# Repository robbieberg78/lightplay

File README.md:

# lightplay
javascript scratch extensions that create blocks to send and receive serial bytes

To see and example, type:

    python -m python_plugin.plugin

If the plugin needs help finding a connected serial device, it will tell you.

Then, with the plugin running, load one of the .sbx files in the examples directory using <a href=http://scratchx.org/> the scratchx website</a>

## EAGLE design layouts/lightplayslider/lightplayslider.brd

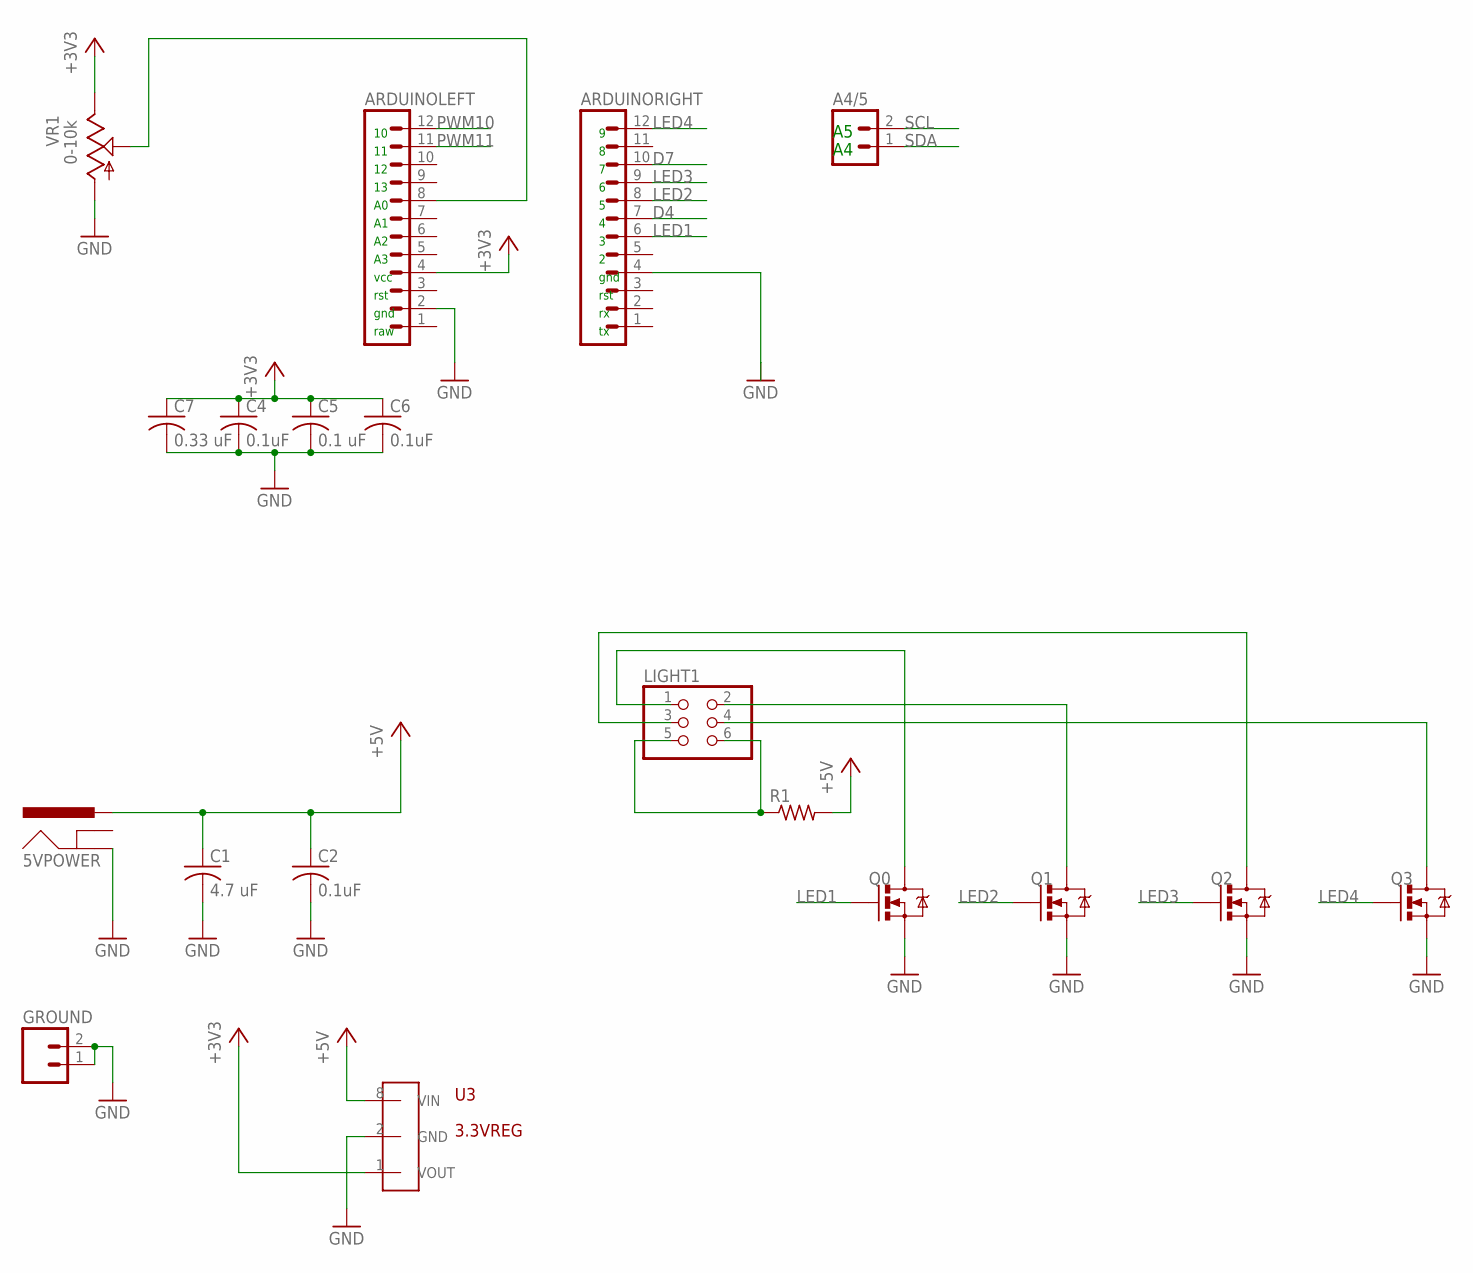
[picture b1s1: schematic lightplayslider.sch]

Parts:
5VPOWER: POWER_JACKPTH; POWER_JACK_PTH
A4/5: M02PTH; 1X02
ARDUINOLEFT: M12PTH; 1X12
ARDUINORIGHT: M12PTH; 1X12
C1: 4.7 uF; C1206
C2, C4, C6: 0.1uF; C0805
C5: 0.1 uF; C0805
C7: 0.33 uF; C1206
GROUND: M02PTH; 1X02
LIGHT1: PINHD-2X3; 2X03
Q0, Q1, Q2, Q3: MOSFET-NCHANNELAO3404A; SOT23-3
R1: R-US_0617/17; 0617/17
U3: 3.3VREG; SO08
VR1: 0-10k; SLIDER-MEDIUM

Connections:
+3V3: ARDUINOLEFT.4, C4.1, C5.1, C6.1, C7.1, U3.1 (VOUT), VR1.TOP (E)
+5V: 5VPOWER.PWR, C1.1, C2.1, R1.2, U3.8 (VIN)
D4: ARDUINORIGHT.7
D7: ARDUINORIGHT.10
GND: 5VPOWER.GND, ARDUINOLEFT.2, ARDUINORIGHT.4, C1.2, C2.2, C4.2, C5.2, C6.2, C7.2, GROUND.1, GROUND.2, Q0.2 (S), Q1.2 (S), Q2.2 (S), Q3.2 (S), U3.2 (GND), VR1.BOTTOM (A)
LED1: ARDUINORIGHT.6, Q0.1 (G)
LED2: ARDUINORIGHT.8, Q1.1 (G)
LED3: ARDUINORIGHT.9, Q2.1 (G)
LED4: ARDUINORIGHT.12, Q3.1 (G)
unnamed: ARDUINOLEFT.8, VR1.WIPER (S)
unnamed: LIGHT1.5, LIGHT1.6, R1.1
unnamed: LIGHT1.1, Q0.3 (D)
unnamed: LIGHT1.2, Q1.3 (D)
unnamed: LIGHT1.3, Q2.3 (D)
unnamed: LIGHT1.4, Q3.3 (D)
PWM10: ARDUINOLEFT.12
PWM11: ARDUINOLEFT.11
SCL: A4/5.2
SDA: A4/5.1

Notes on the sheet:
gnd
rst
raw
vcc

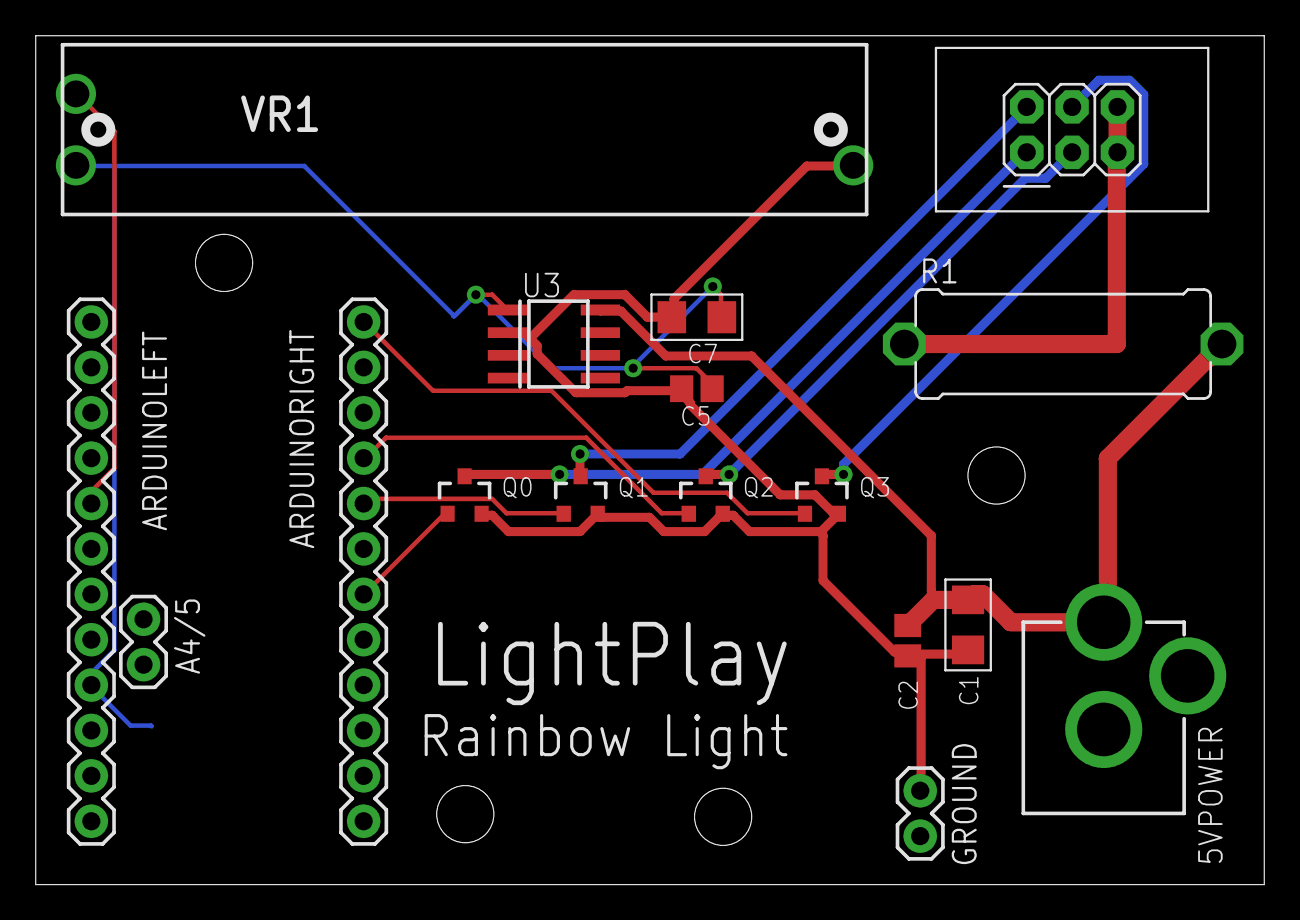
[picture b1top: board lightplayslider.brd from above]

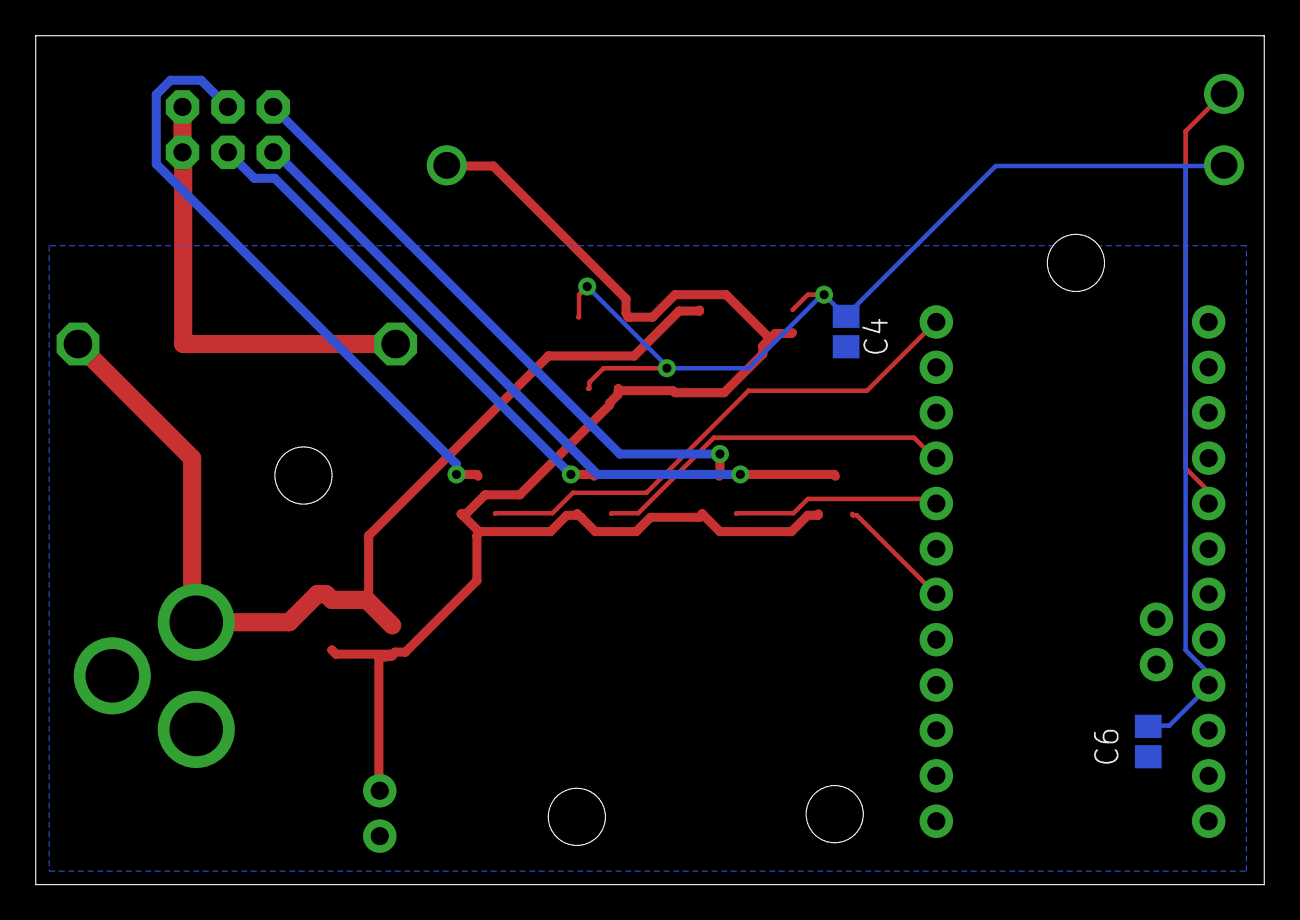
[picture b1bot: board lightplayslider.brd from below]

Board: 2 copper layers, 68.8 x 47.5 mm, 19 parts (2 on the bottom side), 13 nets.

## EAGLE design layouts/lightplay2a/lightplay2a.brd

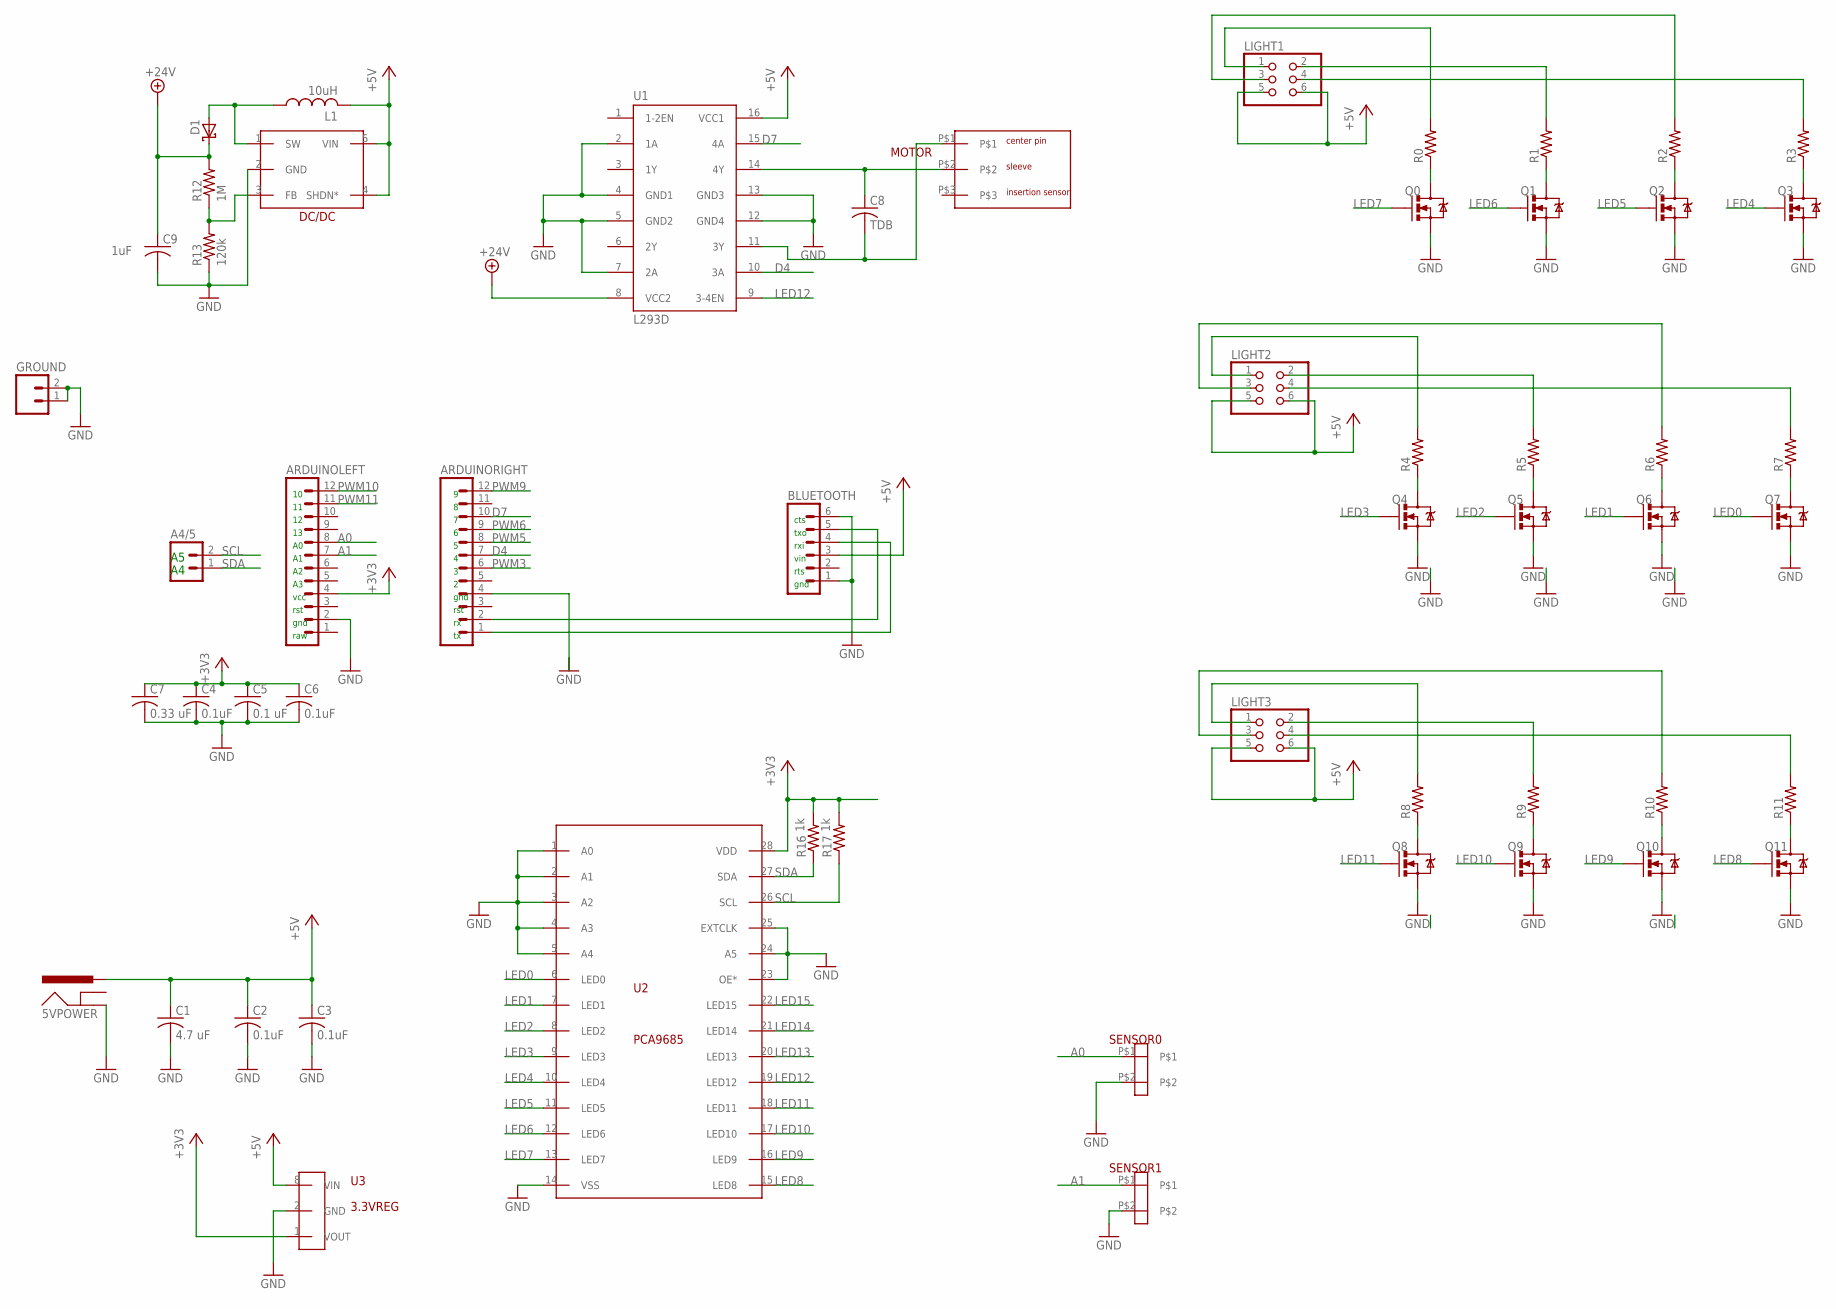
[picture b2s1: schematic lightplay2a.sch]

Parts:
5VPOWER: POWER_JACKPTH; POWER_JACK_PTH
A4/5: M02PTH; 1X02
ARDUINOLEFT: M12PTH; 1X12
ARDUINORIGHT: M12PTH; 1X12
BLUETOOTH: M06SILK_FEMALE_PTH; 1X06
C1: 4.7 uF; C1206
C2, C3, C4, C6: 0.1uF; C0805
C5: 0.1 uF; C0805
C7: 0.33 uF; C1206
C8: TDB; C0805
C9: 1uF; C1206
D1: B120_SHOTTKY_DIODE; DO214AC
DC/DC: LT1615; SOT23-5
GROUND: M02PTH; 1X02
L1: 10uH; INDUCTOR_WURTH
LIGHT1, LIGHT2, LIGHT3: PINHD-2X3; 2X03
MOTOR: PJ-075DH-SMT-TR
Q0, Q1, Q2, Q3, Q4, Q5, Q6, Q7, Q8, Q9, Q10, Q11: MOSFET-NCHANNELAO3404A; SOT23-3
R0, R1, R2, R3, R4, R5, R6, R7, R8, R9, R10, R11: R-US_0617/17; 0617/17
R12: 1M; R0805
R13: 120k; R0805
R16, R17: 1k; R0805
SENSOR0, SENSOR1: 3.5MM_2PIN_SCREWTERMINAL_SPARKFUN; 1X02_3.5_SCREWTERM
U1: L293D; DIL16
U2: PCA9685; TSSOP28
U3: 3.3VREG; SO08

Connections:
+3V3: ARDUINOLEFT.4, C4.1, C5.1, C6.1, C7.1, R16.2, R17.2, U2.28 (VDD), U3.1 (VOUT)
+5V: 5VPOWER.PWR, BLUETOOTH.3, C1.1, C2.1, C3.1, DC/DC.4 (SHDN*), DC/DC.5 (VIN), L1.P$2 (2), LIGHT1.5, LIGHT1.6, LIGHT2.5, LIGHT2.6, LIGHT3.5, LIGHT3.6, U1.16 (VCC1), U3.8 (VIN)
+24V: C9.1, D1.C, R12.2, U1.8 (VCC2)
A0: ARDUINOLEFT.8, SENSOR0.P$1
A1: ARDUINOLEFT.7, SENSOR1.P$1
D4: ARDUINORIGHT.7, U1.10 (3A)
D7: ARDUINORIGHT.10, U1.15 (4A)
GND: 5VPOWER.GND, ARDUINOLEFT.2, ARDUINORIGHT.4, BLUETOOTH.1, BLUETOOTH.6, C1.2, C2.2, C3.2, C4.2, C5.2, C6.2, C7.2, C9.2, DC/DC.2 (GND), GROUND.1, GROUND.2, Q0.2 (S), Q1.2 (S), Q2.2 (S), Q3.2 (S), Q4.2 (S), Q5.2 (S), Q6.2 (S), Q7.2 (S), Q8.2 (S), Q9.2 (S), Q10.2 (S), Q11.2 (S), R13.1, SENSOR0.P$2, SENSOR1.P$2, U1.2 (1A), U1.4 (GND1), U1.5 (GND2), U1.7 (2A), U1.12 (GND4), U1.13 (GND3), U2.1 (A0), U2.2 (A1), U2.3 (A2), U2.4 (A3), U2.5 (A4), U2.14 (VSS), U2.23 (OE*), U2.24 (A5), U2.25 (EXTCLK), U3.2 (GND)
LED0: Q7.1 (G), U2.6 (LED0)
LED1: Q6.1 (G), U2.7 (LED1)
LED2: Q5.1 (G), U2.8 (LED2)
LED3: Q4.1 (G), U2.9 (LED3)
LED4: Q3.1 (G), U2.10 (LED4)
LED5: Q2.1 (G), U2.11 (LED5)
LED6: Q1.1 (G), U2.12 (LED6)
LED7: Q0.1 (G), U2.13 (LED7)
LED8: Q11.1 (G), U2.15 (LED8)
LED9: Q10.1 (G), U2.16 (LED9)
LED10: Q9.1 (G), U2.17 (LED10)
LED11: Q8.1 (G), U2.18 (LED11)
LED12: U1.9 (3-4EN), U2.19 (LED12)
LED13: U2.20 (LED13)
LED14: U2.21 (LED14)
LED15: U2.22 (LED15)
unnamed: Q0.3 (D), R0.1
unnamed: Q1.3 (D), R1.1
unnamed: Q2.3 (D), R2.1
unnamed: C8.1, MOTOR.P$2, U1.14 (4Y)
unnamed: C8.2, MOTOR.P$1, U1.11 (3Y)
unnamed: D1.A, DC/DC.1 (SW), L1.P$1 (1)
unnamed: LIGHT1.1, R0.2
unnamed: Q3.3 (D), R3.1
unnamed: LIGHT1.2, R1.2
unnamed: ARDUINORIGHT.2, BLUETOOTH.5
unnamed: ARDUINORIGHT.1, BLUETOOTH.4
unnamed: Q4.3 (D), R4.1
unnamed: LIGHT1.3, R2.2
unnamed: LIGHT1.4, R3.2
unnamed: Q5.3 (D), R5.1
unnamed: Q6.3 (D), R6.1
unnamed: Q7.3 (D), R7.1
unnamed: LIGHT2.1, R4.2
unnamed: LIGHT2.2, R5.2
unnamed: LIGHT2.3, R6.2
unnamed: LIGHT2.4, R7.2
unnamed: Q8.3 (D), R8.1
unnamed: Q9.3 (D), R9.1
unnamed: Q10.3 (D), R10.1
unnamed: Q11.3 (D), R11.1
unnamed: LIGHT3.1, R8.2
unnamed: LIGHT3.2, R9.2
unnamed: LIGHT3.3, R10.2
unnamed: LIGHT3.4, R11.2
unnamed: DC/DC.3 (FB), R12.1, R13.2
PWM3: ARDUINORIGHT.6
PWM5: ARDUINORIGHT.8
PWM6: ARDUINORIGHT.9
PWM9: ARDUINORIGHT.12
PWM10: ARDUINOLEFT.12
PWM11: ARDUINOLEFT.11
SCL: A4/5.2, R17.1, U2.26 (SCL)
SDA: A4/5.1, R16.1, U2.27 (SDA)

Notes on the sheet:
gnd
rst
raw
vcc
rts
vin
rxi
txo
cts

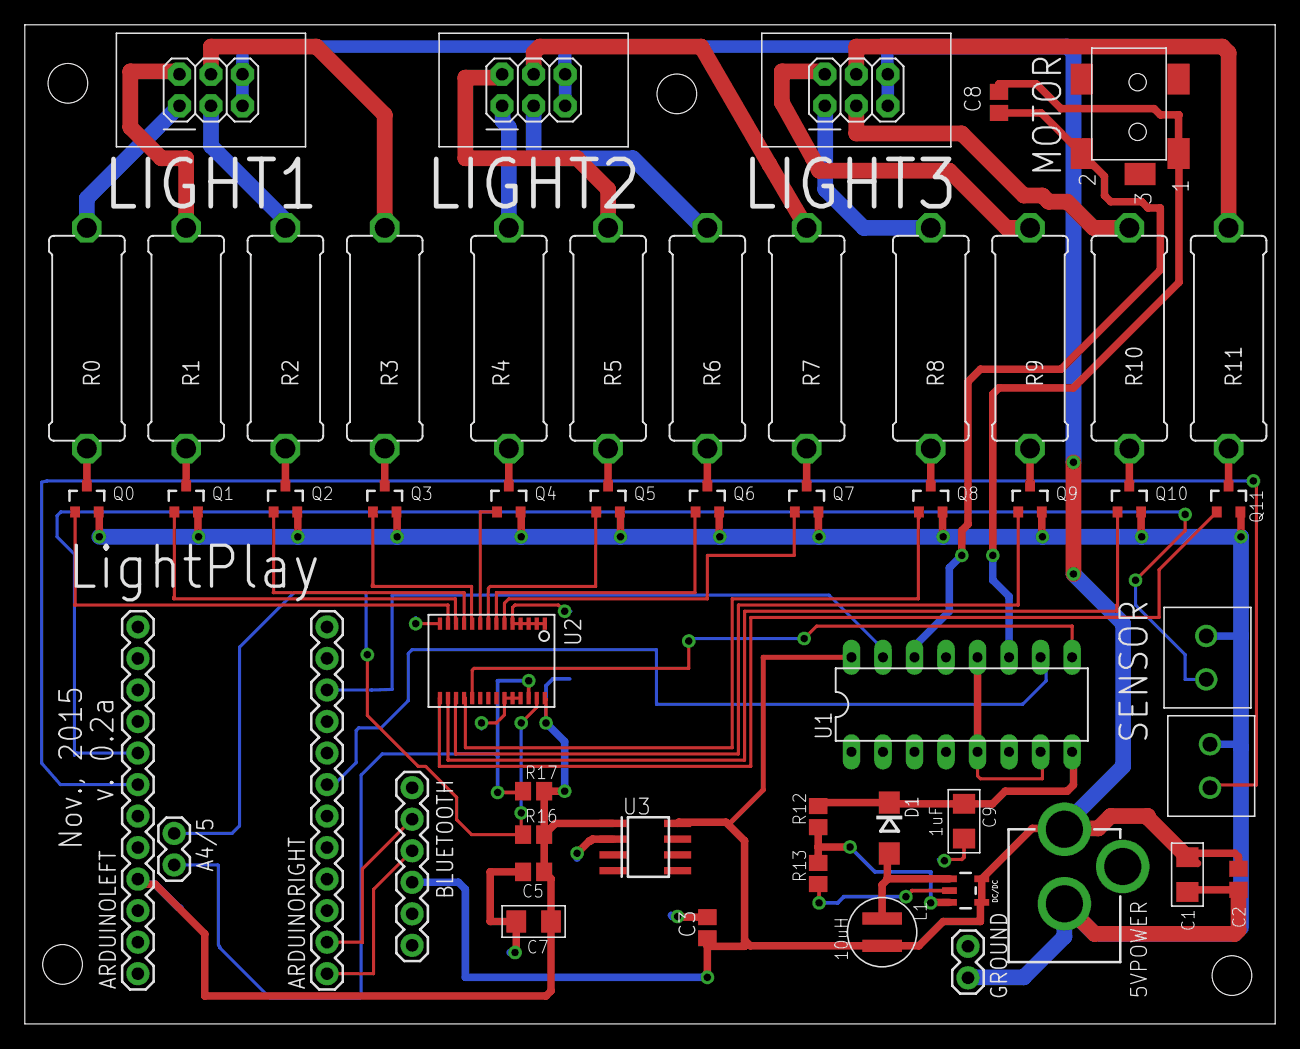
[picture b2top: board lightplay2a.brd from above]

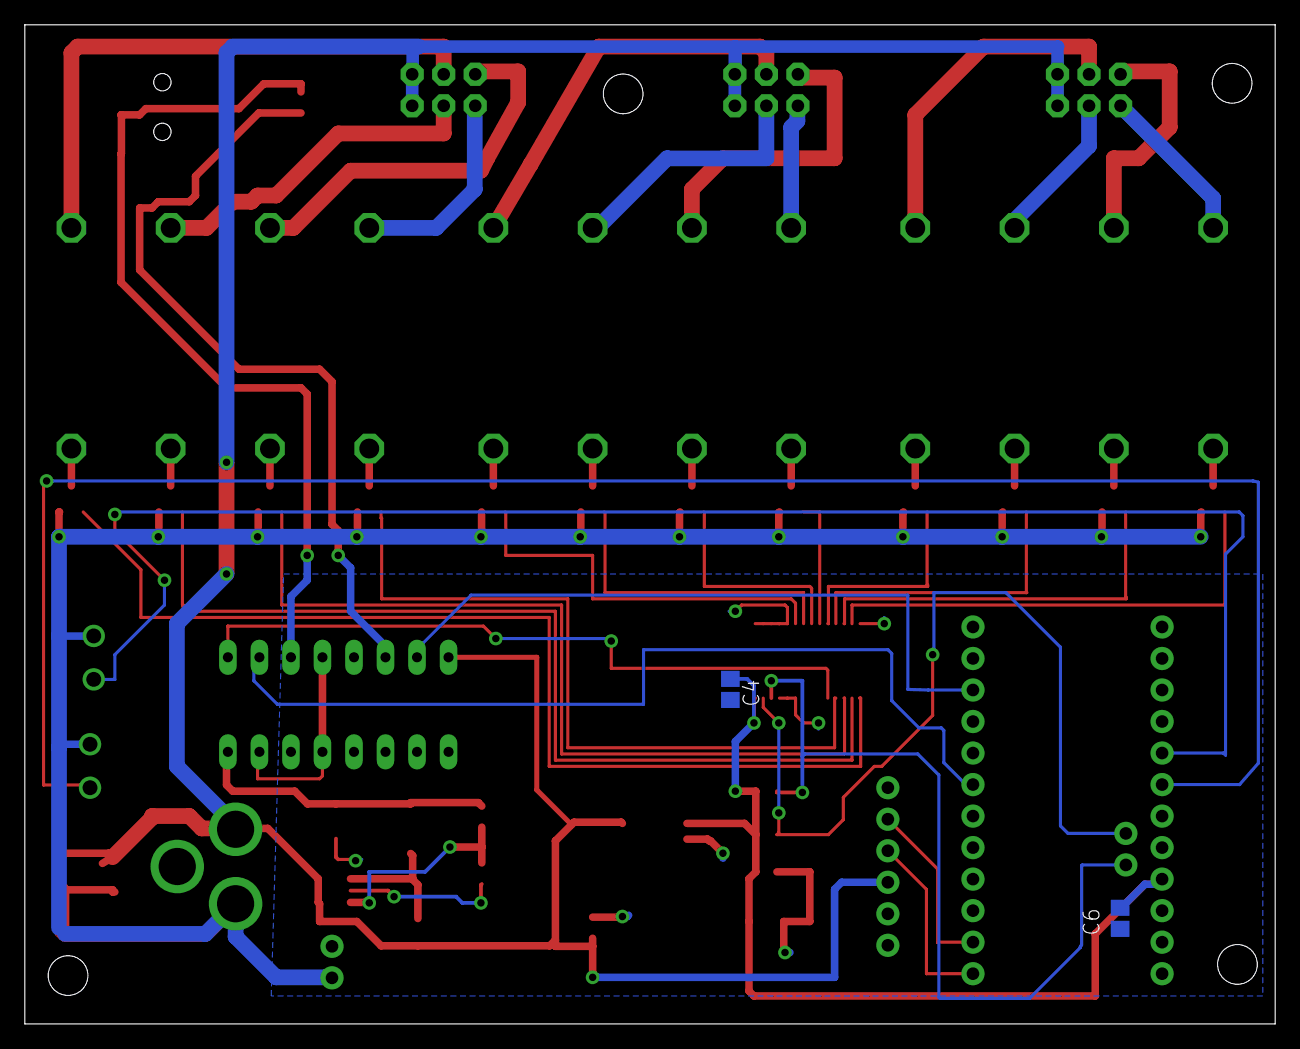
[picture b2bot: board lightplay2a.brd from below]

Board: 2 copper layers, 100.8 x 80.5 mm, 55 parts (2 on the bottom side), 53 nets.

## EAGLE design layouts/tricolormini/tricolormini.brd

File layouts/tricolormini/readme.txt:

The zip file tricolormini.zip contains the following files:1 readme.txt7 Gerber Files (all are unmirrored) :1) tricolormini.dim - contains the board outline, ; please use this file to determine the board shape!2) tricolormini.cmp - contains the component side of the two layer board.3) tricolormini.sol - contains the solder side of the two layer board.4) tricolormini.plc - contains the component side of the silkscreen legend.5) tricolormini.pls - contains the solder side of the silkscreen legend.6) tricolormini.stc - contains the component side of the solder mask.7) tricolormini.sts - contains the solder side of the solder mask.2 drill files:1) tricolormini.dri2) tricolormini.drd

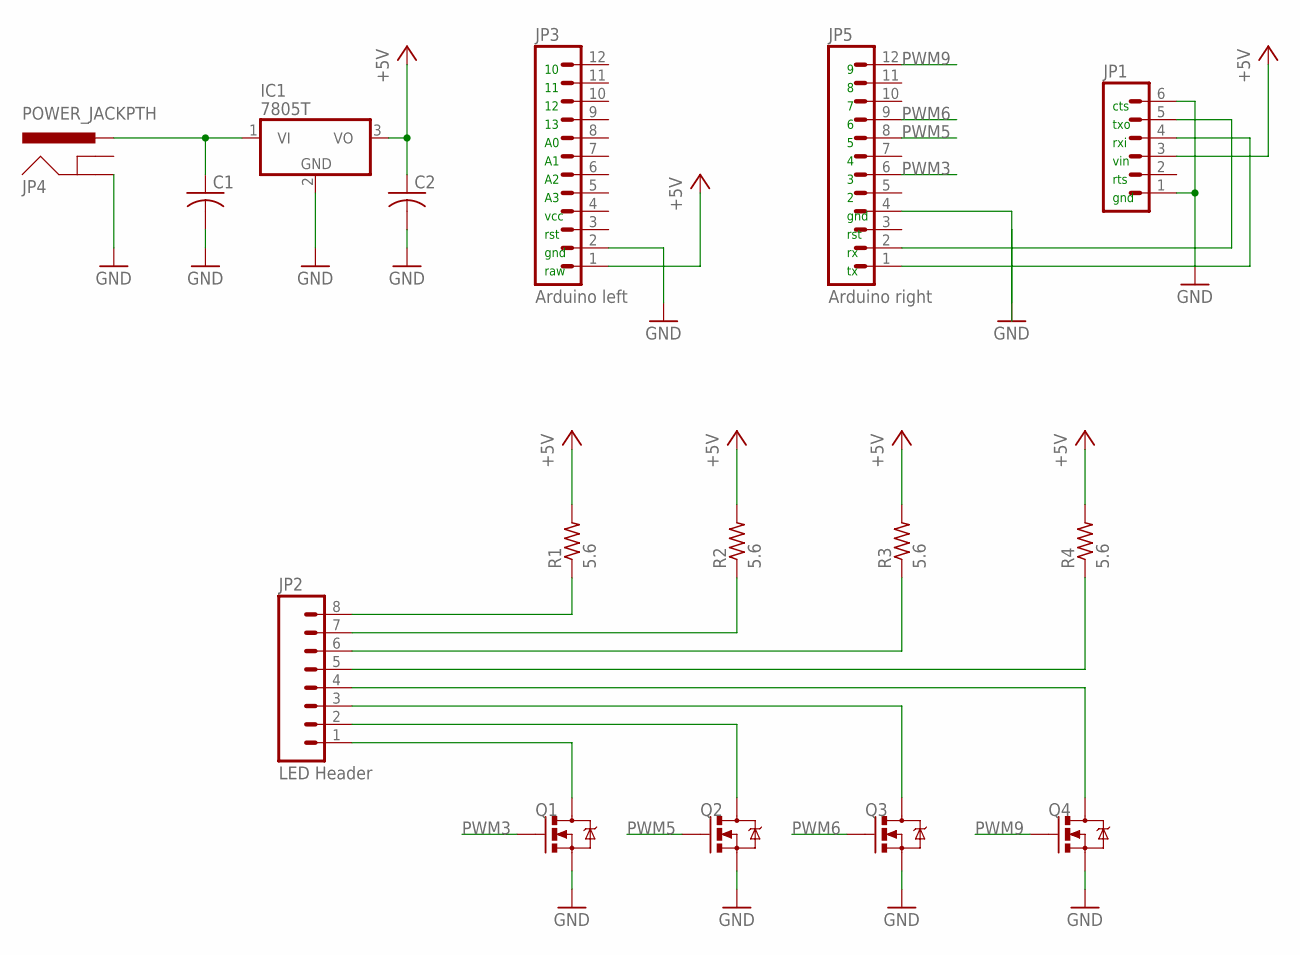
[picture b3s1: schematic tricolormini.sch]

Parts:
C1, C2: C-USC1206; C1206
IC1: 7805T; TO220H
JP1: M06SILK_FEMALE_PTH; 1X06
JP2: LED Header; 1X08_ROUND
JP3: Arduino left; 1X12
JP4: POWER_JACKPTH; POWER_JACK_PTH
JP5: Arduino right; 1X12
Q1, Q2, Q3, Q4: MOSFET-NCHANNELAO3404A; SOT23-3
R1, R2, R3, R4: 5.6; 0207/10

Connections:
+5V: C2.1, IC1.3 (VO), JP1.3, JP3.1, R1.2, R2.2, R3.2, R4.2
GND: C1.2, C2.2, IC1.2 (GND), JP1.1, JP1.6, JP3.2, JP4.GND, JP5.4, Q1.2 (S), Q2.2 (S), Q3.2 (S), Q4.2 (S)
unnamed: C1.1, IC1.1 (VI), JP4.PWR
unnamed: JP2.1, Q1.3 (D)
unnamed: JP2.2, Q2.3 (D)
unnamed: JP2.3, Q3.3 (D)
unnamed: JP2.4, Q4.3 (D)
unnamed: JP2.8, R1.1
unnamed: JP2.7, R2.1
unnamed: JP2.6, R3.1
unnamed: JP2.5, R4.1
unnamed: JP1.5, JP5.2
unnamed: JP1.4, JP5.1
PWM3: JP5.6, Q1.1 (G)
PWM5: JP5.8, Q2.1 (G)
PWM6: JP5.9, Q3.1 (G)
PWM9: JP5.12, Q4.1 (G)

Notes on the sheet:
gnd
rst
raw
vcc
rts
vin
rxi
txo
cts

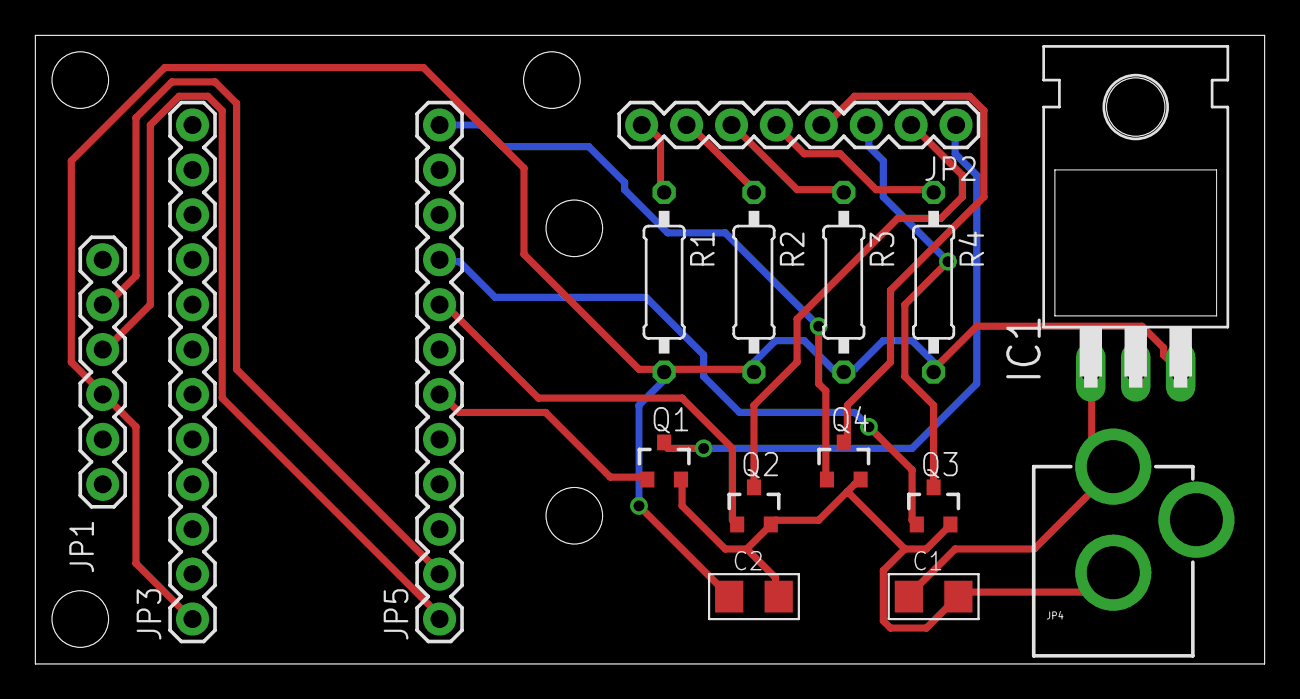
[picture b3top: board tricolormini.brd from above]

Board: 2 copper layers, 69.5 x 35.5 mm, 16 parts (0 on the bottom side), 17 nets.

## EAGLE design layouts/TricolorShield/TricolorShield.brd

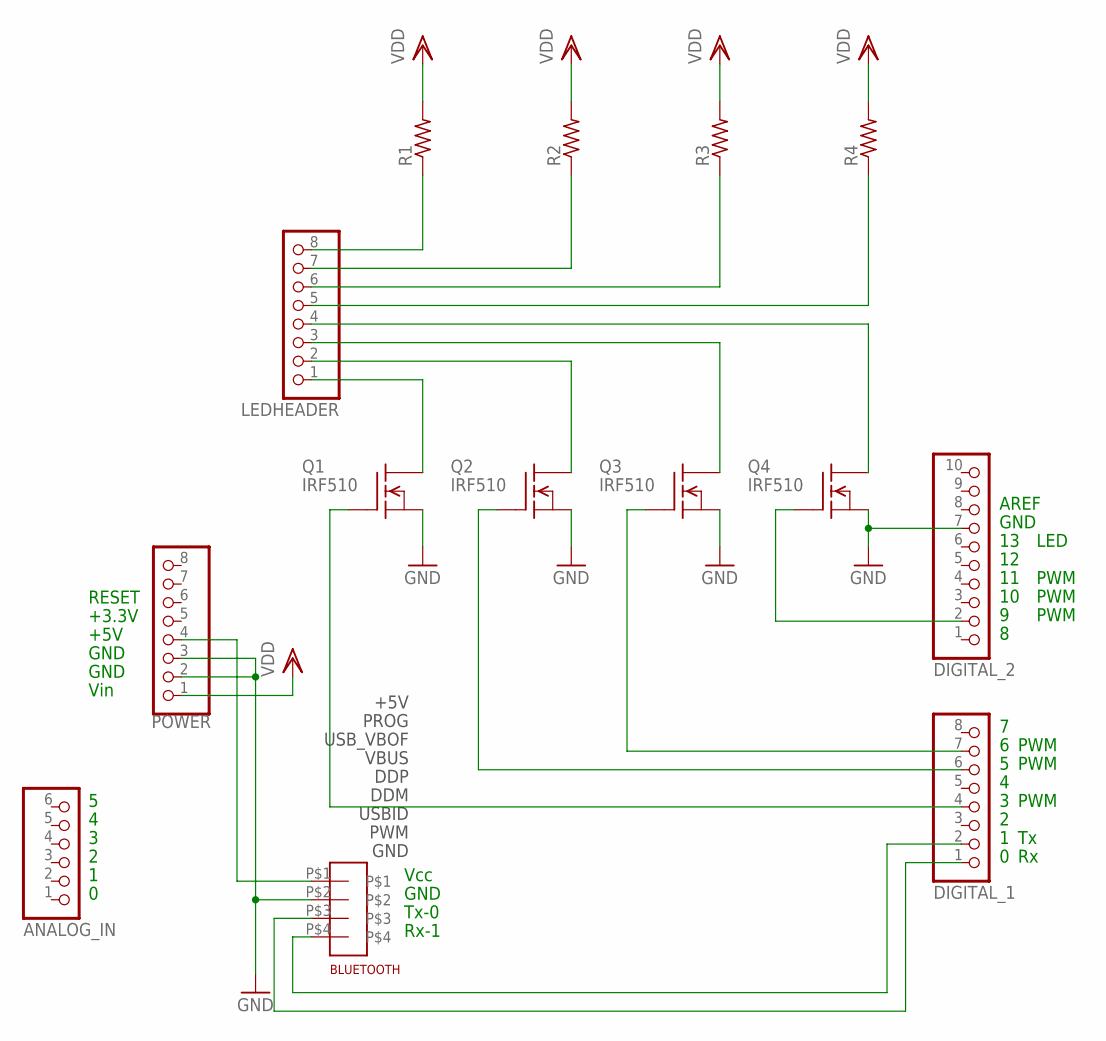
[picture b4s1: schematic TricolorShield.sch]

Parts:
ANALOG_IN: PINHD-1X6TH; 1X06-TH
BLUETOOTH: 4PADS_ROBBIE; 1X04_ROBBIE
DIGITAL_1: PINHD-1X8TH; 1X08-TH
DIGITAL_2: PINHD-1X10TH; 1X10-TH
LEDHEADER: PINHD-1X8TH; 1X08-TH
POWER: PINHD-1X8TH; 1X08-TH
Q1, Q2, Q3, Q4: IRF510; TO220
R1, R2, R3, R4: R-US_0922/22; 0922/22

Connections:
GND: BLUETOOTH.P$2, DIGITAL_2.7, POWER.2, POWER.3, Q1.3 (S), Q2.3 (S), Q3.3 (S), Q4.3 (S)
unnamed: DIGITAL_1.4, Q1.1 (G)
unnamed: LEDHEADER.8, R1.1
unnamed: LEDHEADER.1, Q1.2 (D)
unnamed: LEDHEADER.7, R2.1
unnamed: DIGITAL_1.6, Q2.1 (G)
unnamed: DIGITAL_1.7, Q3.1 (G)
unnamed: DIGITAL_2.2, Q4.1 (G)
unnamed: LEDHEADER.2, Q2.2 (D)
unnamed: LEDHEADER.6, R3.1
unnamed: LEDHEADER.3, Q3.2 (D)
unnamed: LEDHEADER.5, R4.1
unnamed: LEDHEADER.4, Q4.2 (D)
unnamed: BLUETOOTH.P$3, DIGITAL_1.1
unnamed: BLUETOOTH.P$1, POWER.4
unnamed: BLUETOOTH.P$4, DIGITAL_1.2
VDD: POWER.1, R1.2, R2.2, R3.2, R4.2

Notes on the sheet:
Vin
GND
+5V
+3.3V
RESET
PWM
AREF
LED
PROG
USB_VBOF
VBUS
DDP
DDM
USBID
Vcc
Tx-0
Rx-1

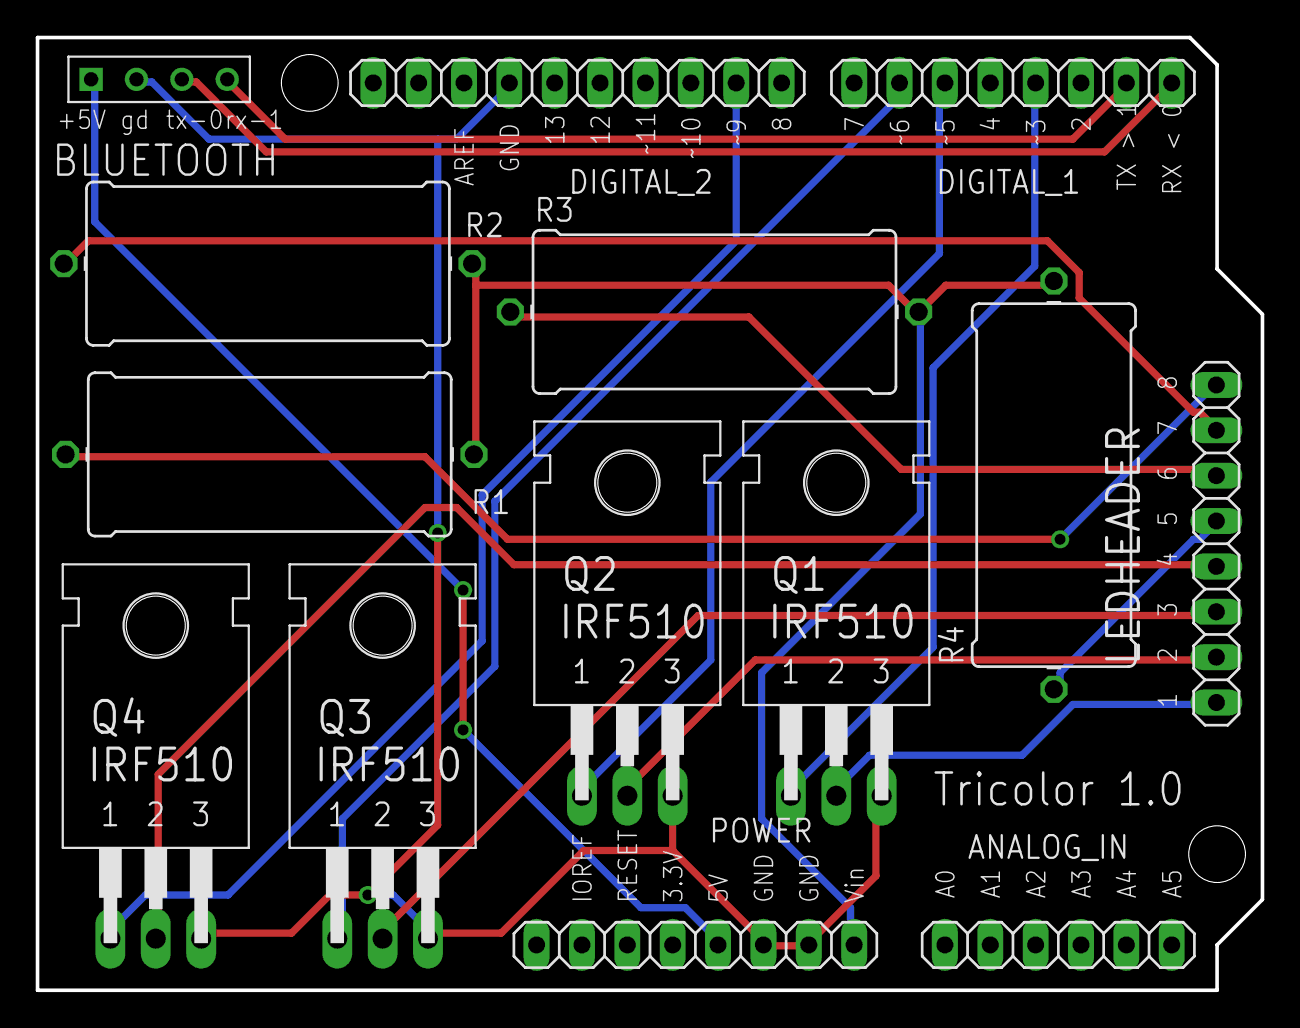
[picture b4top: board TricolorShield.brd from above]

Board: 2 copper layers, 68.6 x 53.3 mm, 14 parts (0 on the bottom side), 17 nets.

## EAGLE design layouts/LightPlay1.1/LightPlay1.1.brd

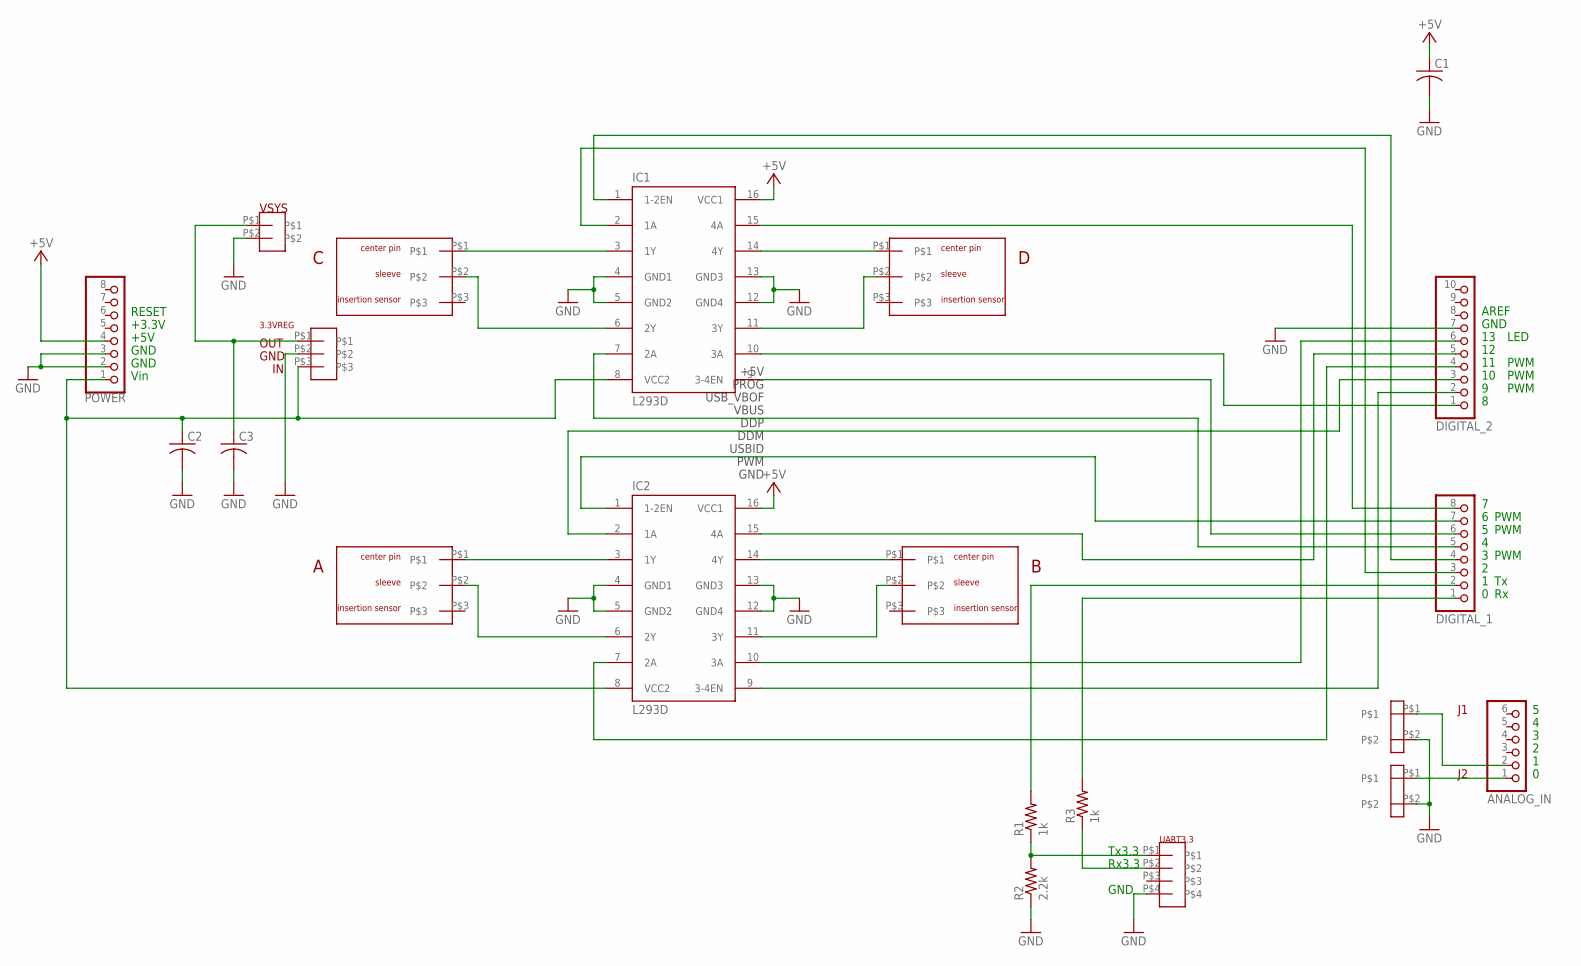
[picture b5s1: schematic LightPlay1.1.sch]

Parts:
3.3VREG: LP38691_33REG; TO-252
A: PJ-075DH-SMT-TR
ANALOG_IN: PINHD-1X6TH; 1X06-TH
B: PJ-075DH-SMT-TR
C: PJ-075DH-SMT-TR
C1, C2, C3: C-USC1206; C1206
D: PJ-075DH-SMT-TR
DIGITAL_1: PINHD-1X8TH; 1X08-TH
DIGITAL_2: PINHD-1X10TH; 1X10-TH
IC1, IC2: L293D; DIL16
J1, J2: 3.5MM_2PIN_SCREWTERMINAL_SPARKFUN; 1X02_3.5_SCREWTERM
POWER: PINHD-1X8TH; 1X08-TH
R1, R3: 1k; M1206
R2: 2.2k; M1206
UART3.3: 4PADS_ROBBIE; 1X04_ROBBIE
VSYS: 1X2HEADER_ROBBIE

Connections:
+5V: C1.1, IC1.16 (VCC1), IC2.16 (VCC1), POWER.4
GND: 3.3VREG.P$2, C1.2, C2.2, C3.2, DIGITAL_2.7, IC1.4 (GND1), IC1.5 (GND2), IC1.12 (GND4), IC1.13 (GND3), IC2.4 (GND1), IC2.5 (GND2), IC2.12 (GND4), IC2.13 (GND3), J1.P$2, J2.P$2, POWER.2, POWER.3, R2.1, UART3.3.P$4, VSYS.P$2
unnamed: D.P$2, IC1.11 (3Y)
unnamed: ANALOG_IN.1, J2.P$1
unnamed: D.P$1, IC1.14 (4Y)
unnamed: B.P$1, IC2.14 (4Y)
unnamed: ANALOG_IN.2, J1.P$1
unnamed: 3.3VREG.P$3, C2.1, IC1.8 (VCC2), IC2.8 (VCC2), POWER.1
unnamed: B.P$2, IC2.11 (3Y)
unnamed: C.P$1, IC1.3 (1Y)
unnamed: C.P$2, IC1.6 (2Y)
unnamed: A.P$1, IC2.3 (1Y)
unnamed: A.P$2, IC2.6 (2Y)
unnamed: DIGITAL_1.4, IC1.1 (1-2EN)
unnamed: DIGITAL_1.6, IC1.9 (3-4EN)
unnamed: DIGITAL_1.7, IC2.1 (1-2EN)
unnamed: DIGITAL_2.2, IC2.9 (3-4EN)
unnamed: DIGITAL_1.3, IC1.2 (1A)
unnamed: DIGITAL_1.5, IC1.7 (2A)
unnamed: DIGITAL_1.8, IC1.15 (4A)
unnamed: DIGITAL_2.1, IC1.10 (3A)
unnamed: DIGITAL_2.3, IC2.2 (1A)
unnamed: DIGITAL_2.4, IC2.7 (2A)
unnamed: DIGITAL_2.5, IC2.15 (4A)
unnamed: DIGITAL_2.6, IC2.10 (3A)
unnamed: 3.3VREG.P$1, C3.1, VSYS.P$1
unnamed: R1.1, R2.2, UART3.3.P$1
unnamed: DIGITAL_1.2, R1.2
unnamed: DIGITAL_1.1, R3.2
unnamed: R3.1, UART3.3.P$2

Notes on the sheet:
Vin
GND
+5V
+3.3V
RESET
PWM
AREF
LED
PROG
USB_VBOF
VBUS
DDP
DDM
USBID
Tx3.3
Rx3.3

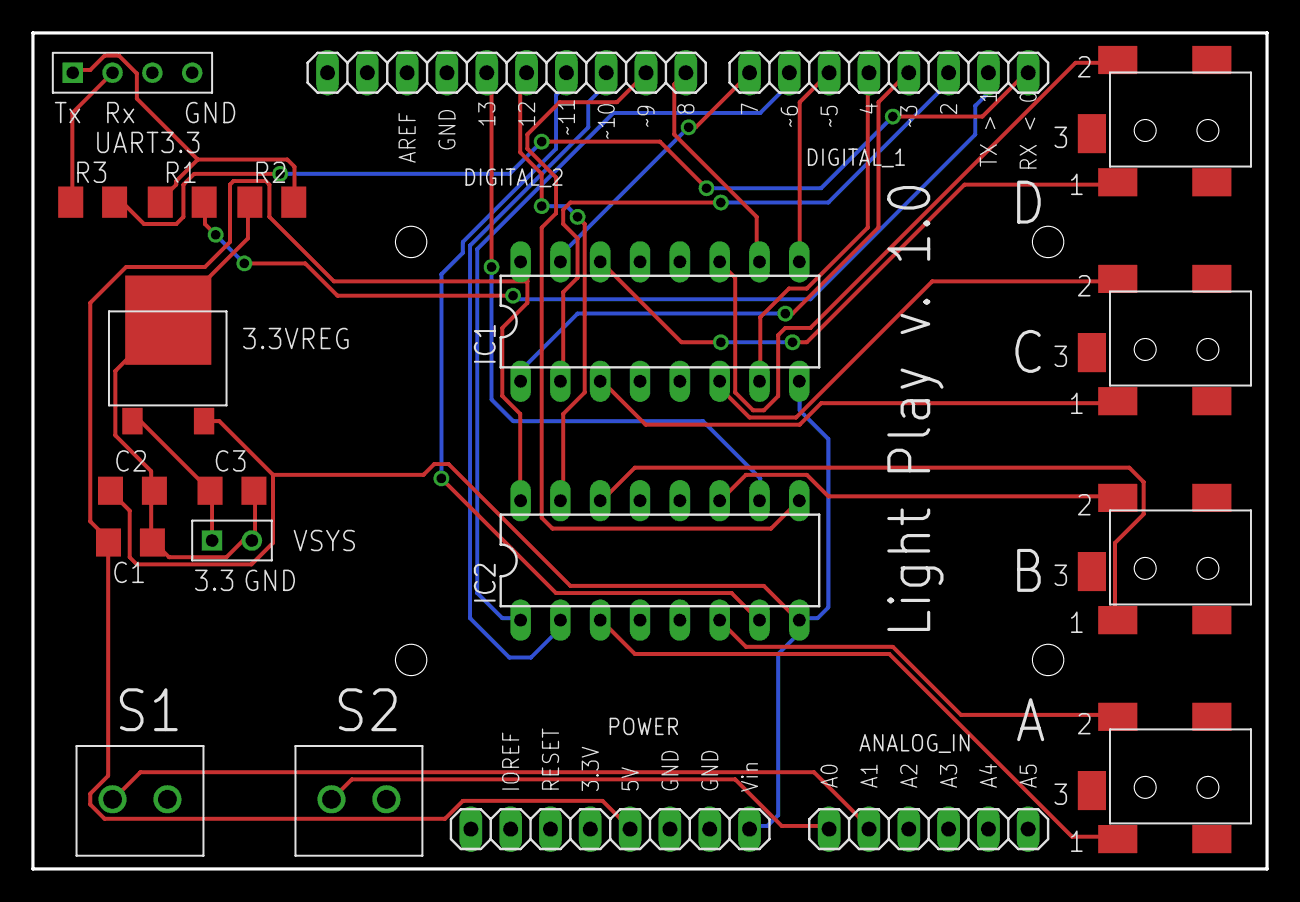
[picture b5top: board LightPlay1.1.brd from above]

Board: 2 copper layers, 78.7 x 53.3 mm, 21 parts (0 on the bottom side), 30 nets.

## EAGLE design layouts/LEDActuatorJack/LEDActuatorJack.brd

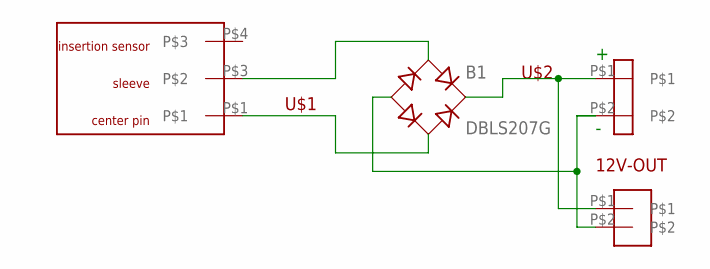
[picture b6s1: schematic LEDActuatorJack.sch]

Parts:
12V-OUT: 1X2HEADER_ROBBIE
B1: DBLS207G; DBS
U$1: PJ-014CH-SMT
U$2: 3.5MM_2PIN_SCREWTERMINAL_SPARKFUN; 1X02_3.5_SCREWTERM

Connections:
unnamed: B1.AC1, U$1.P$3
unnamed: B1.AC2, U$1.P$1
unnamed: 12V-OUT.P$1, B1.+, U$2.P$1
unnamed: 12V-OUT.P$2, B1.-, U$2.P$2

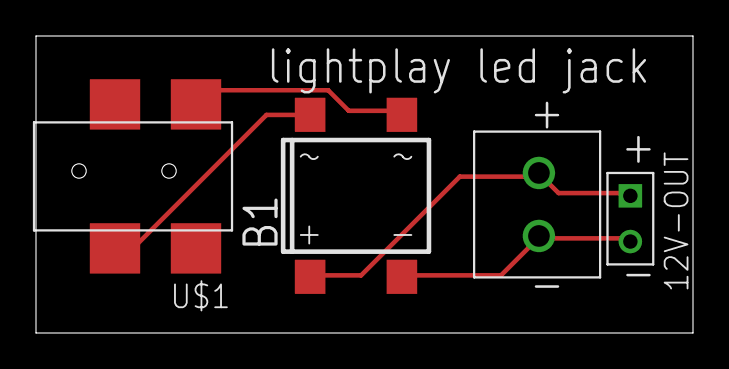
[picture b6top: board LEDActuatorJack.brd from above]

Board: 2 copper layers, 36.5 x 16.5 mm, 4 parts (0 on the bottom side), 4 nets.

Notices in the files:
parts and their libraries:
SparkFun-Connectors: Licensing: Creative Commons ShareAlike 4.0 International - https://creativecommons.org/licenses/by-sa/4.0
